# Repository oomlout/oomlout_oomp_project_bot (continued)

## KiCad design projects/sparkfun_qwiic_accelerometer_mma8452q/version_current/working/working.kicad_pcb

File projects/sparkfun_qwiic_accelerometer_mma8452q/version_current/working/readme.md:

# Qwiic_Accelerometer_MMA8452Q by sparkfun  
This is a harvested standardized copy of a project from github.  
The original project can be found at:  
https://github.com/sparkfun/Qwiic_Accelerometer_MMA8452Q  
Please consult that link for additional, details, files, and license information.  
Note: It was auto harvested and if the original repo had more than one board file or anything out of the ordinary the files here are likely not representative.

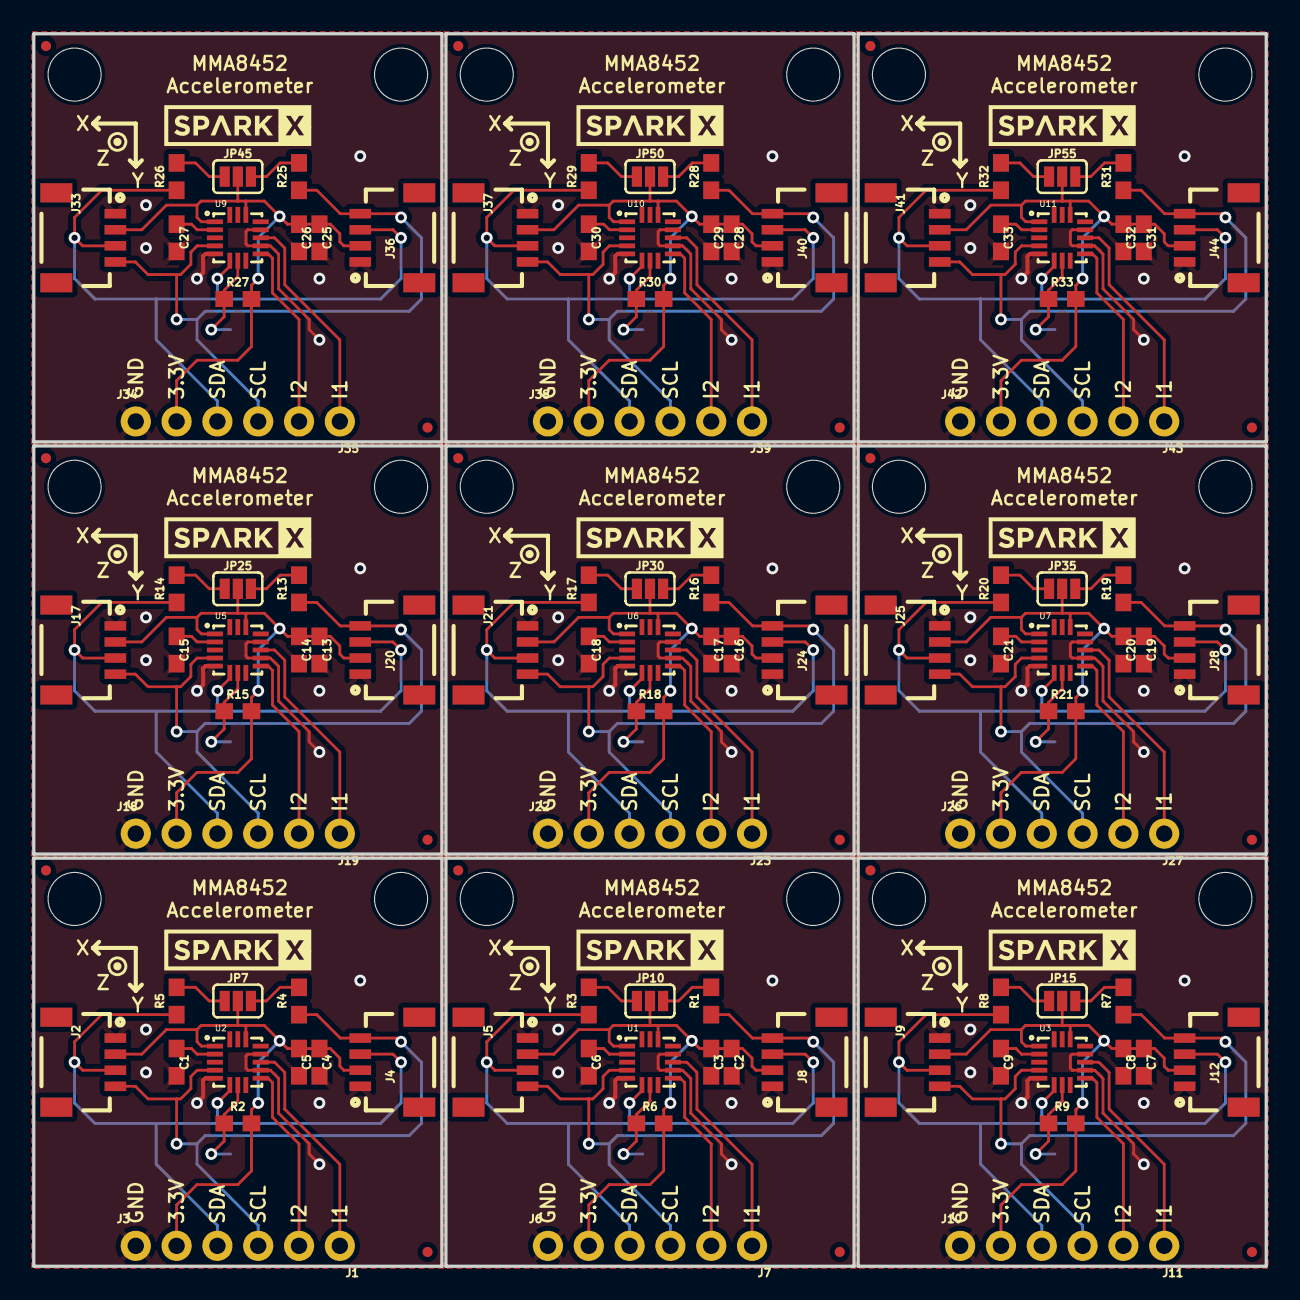
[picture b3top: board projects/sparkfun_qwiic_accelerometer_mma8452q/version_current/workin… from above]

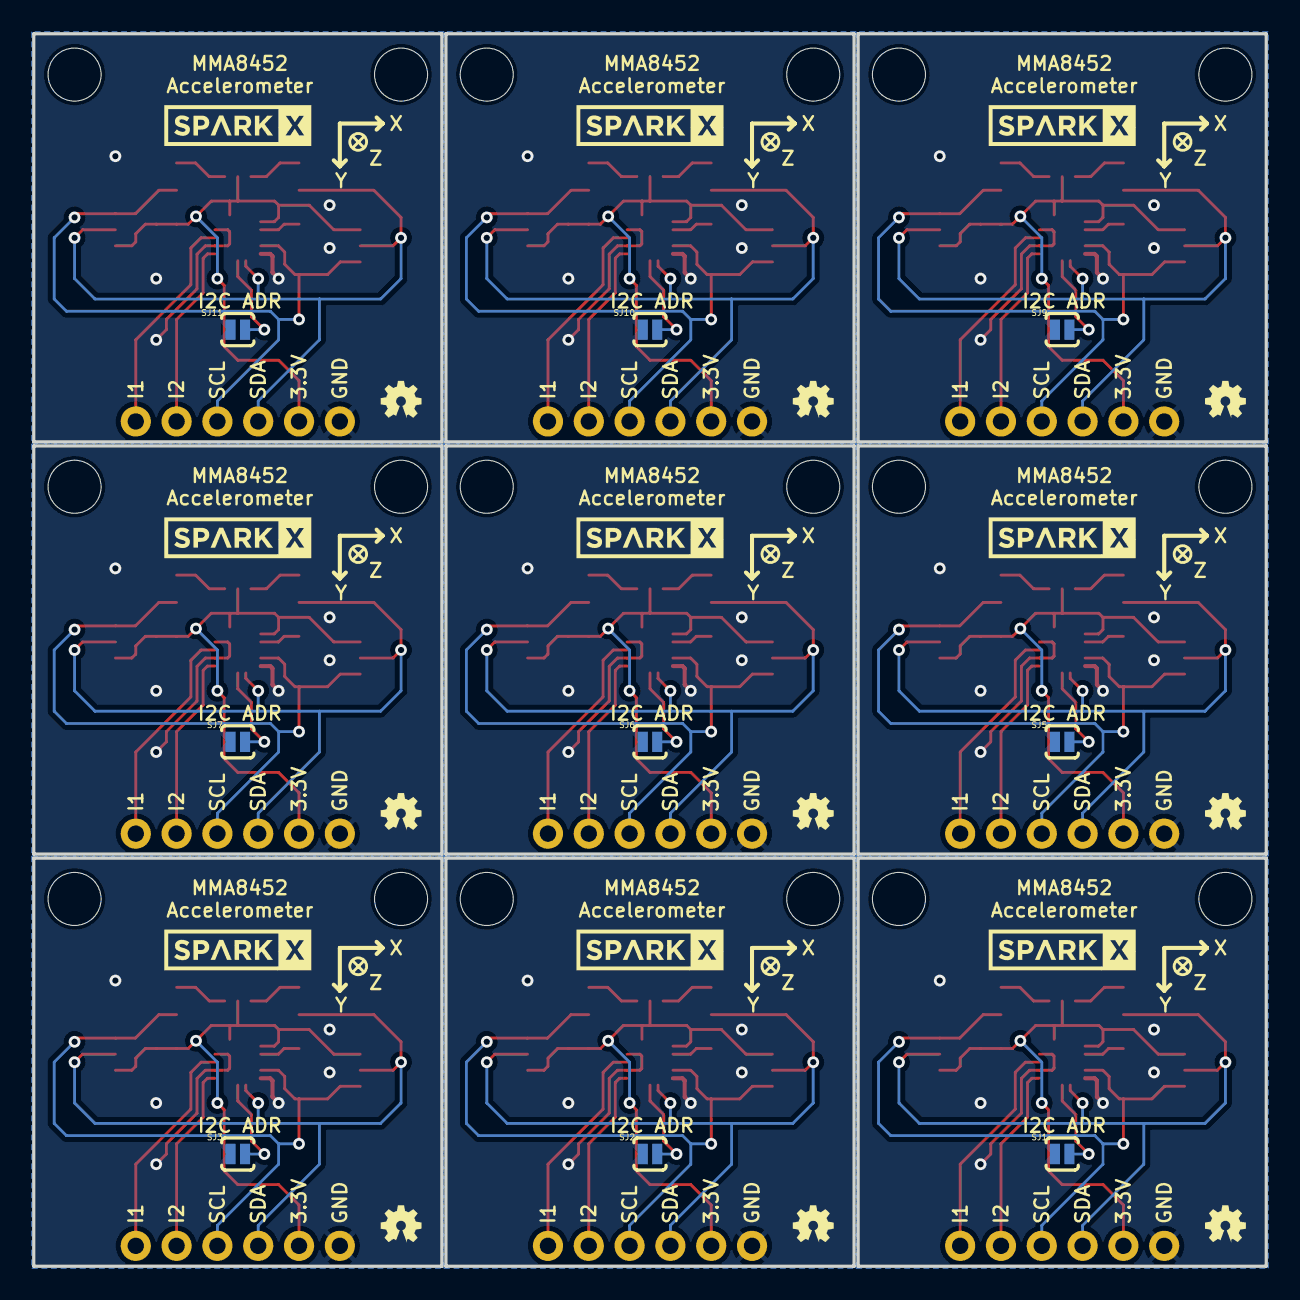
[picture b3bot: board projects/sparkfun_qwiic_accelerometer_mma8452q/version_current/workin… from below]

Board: 2 copper layers, 76.7 x 76.7 mm, 180 parts (27 on the bottom side), 90 nets.

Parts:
C1, C2, C4, C6, C7, C9, C13, C15, C16, C18, C19, C21, C25, C27, C28, C30, C31, C33: 0.1uF; 0603
C3, C5, C8, C14, C17, C20, C26, C29, C32: 4.7uF; 0603
J1, J7, J11, J19, J23, J27, J35, J39, J43: 1X02_NO_SILK
J2, J4, J5, J8, J9, J12, J17, J20, J21, J24, J25, J28, J33, J36, J37, J40, J41, J44: SMD; 1X04_1MM_RA
J3, J6, J10, J18, J22, J26, J34, J38, J42: PTH; 1X04_NO_SILK
JP1, JP3, JP4, JP5, JP11, JP12, JP21, JP22, JP26, JP27, JP31, JP32, JP41, JP42, JP46, JP47, JP51, JP52: STAND-OFF
JP2, JP6, JP8, JP9, JP13, JP14, JP23, JP24, JP28, JP29, JP33, JP34, JP43, JP44, JP48, JP49, JP53, JP54: FIDUCIALUFIDUCIAL; MICRO-FIDUCIAL
JP7, JP10, JP15, JP25, JP30, JP35, JP45, JP50, JP55: SMT-JUMPER_3_2-NC_PASTE_SILK
LOGO1, LOGO2, LOGO3, LOGO5, LOGO6, LOGO7, LOGO9, LOGO10, LOGO11: OSHW-LOGOMINI; OSHW-LOGO-MINI
R1, R3, R4, R5, R7, R8, R13, R14, R16, R17, R19, R20, R25, R26, R28, R29, R31, R32: 4.7k; 0603
R2, R6, R9, R15, R18, R21, R27, R30, R33: 10k; 0603
SJ1, SJ2, SJ3, SJ5, SJ6, SJ7, SJ9, SJ10, SJ11: SJ_2S-NO
U1, U2, U3, U5, U6, U7, U9, U10, U11: MMA8452Q; QFN-16_0.5MM
U$1, U$2, U$3, U$4, U$5, U$6, U$9, U$10, U$11, U$12, U$13, U$14, U$17, U$18, U$19, U$20, U$21, U$22: SPARKX-LOGO4; SPARKX-MEDIUM

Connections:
3.3V: C4.1, C5.1, J2.2, J3.2, J4.2, JP7.2, R2.2, U2.1, U2.14
3.3V1: C2.1, C3.1, J5.2, J6.2, J8.2, JP10.2, R6.2, U1.1, U1.14
3.3V2: C7.1, C8.1, J9.2, J10.2, J12.2, JP15.2, R9.2, U3.1, U3.14
3.3V4: C13.1, C14.1, J17.2, J18.2, J20.2, JP25.2, R15.2, U5.1, U5.14
3.3V5: C16.1, C17.1, J21.2, J22.2, J24.2, JP30.2, R18.2, U6.1, U6.14
3.3V6: C19.1, C20.1, J25.2, J26.2, J28.2, JP35.2, R21.2, U7.1, U7.14
3.3V8: C25.1, C26.1, J33.2, J34.2, J36.2, JP45.2, R27.2, U9.1, U9.14
3.3V9: C28.1, C29.1, J37.2, J38.2, J40.2, JP50.2, R30.2, U10.1, U10.14
3.3V10: C31.1, C32.1, J41.2, J42.2, J44.2, JP55.2, R33.2, U11.1, U11.14
BYP: C1.1, U2.2
BYP1: C6.1, U1.2
BYP2: C9.1, U3.2
BYP4: C15.1, U5.2
BYP5: C18.1, U6.2
BYP6: C21.1, U7.2
BYP8: C27.1, U9.2
BYP9: C30.1, U10.2
BYP10: C33.1, U11.2
GND: C1.2, C4.2, C5.2, J2.1, J3.1, J4.1, SJ1.1, U2.5, U2.10, U2.12
GND1: C2.2, C3.2, C6.2, J5.1, J6.1, J8.1, SJ2.1, U1.5, U1.10, U1.12
GND2: C7.2, C8.2, C9.2, J9.1, J10.1, J12.1, SJ3.1, U3.5, U3.10, U3.12
GND4: C13.2, C14.2, C15.2, J17.1, J18.1, J20.1, SJ5.1, U5.5, U5.10, U5.12
GND5: C16.2, C17.2, C18.2, J21.1, J22.1, J24.1, SJ6.1, U6.5, U6.10, U6.12
GND6: C19.2, C20.2, C21.2, J25.1, J26.1, J28.1, SJ7.1, U7.5, U7.10, U7.12
GND8: C25.2, C26.2, C27.2, J33.1, J34.1, J36.1, SJ9.1, U9.5, U9.10, U9.12
GND9: C28.2, C29.2, C30.2, J37.1, J38.1, J40.1, SJ10.1, U10.5, U10.10, U10.12
GND10: C31.2, C32.2, C33.2, J41.1, J42.1, J44.1, SJ11.1, U11.5, U11.10, U11.12
INT1: J1.1, U2.11
INT2: J1.2, U2.9
INT3: J7.2, U1.9
INT4: J7.1, U1.11
INT5: J11.2, U3.9
INT6: J11.1, U3.11
INT9: J19.2, U5.9
INT10: J19.1, U5.11
INT11: J23.2, U6.9
INT12: J23.1, U6.11
INT13: J27.2, U7.9
INT14: J27.1, U7.11
INT17: J35.2, U9.9
INT18: J35.1, U9.11
INT19: J39.2, U10.9
INT20: J39.1, U10.11
INT21: J43.2, U11.9
INT22: J43.1, U11.11
unnamed: JP7.1, R5.2
unnamed: JP7.3, R4.2
unnamed: JP10.1, R3.2
unnamed: JP10.3, R1.2
unnamed: JP15.1, R8.2
unnamed: JP15.3, R7.2
unnamed: JP25.1, R14.2
unnamed: JP25.3, R13.2
unnamed: JP30.1, R17.2
unnamed: JP30.3, R16.2
unnamed: JP35.1, R20.2
unnamed: JP35.3, R19.2
unnamed: JP45.1, R26.2
unnamed: JP45.3, R25.2
unnamed: JP50.1, R29.2
unnamed: JP50.3, R28.2
unnamed: JP55.1, R32.2
unnamed: JP55.3, R31.2
SA0: R2.1, SJ1.2, U2.7
SA1: R6.1, SJ2.2, U1.7
SA2: R9.1, SJ3.2, U3.7
SA4: R15.1, SJ5.2, U5.7
SA5: R18.1, SJ6.2, U6.7
SA6: R21.1, SJ7.2, U7.7
SA8: R27.1, SJ9.2, U9.7
SA9: R30.1, SJ10.2, U10.7
SA10: R33.1, SJ11.2, U11.7
SCL: J2.4, J3.4, J4.4, R4.1, U2.4
SCL1: J5.4, J6.4, J8.4, R1.1, U1.4
SCL2: J9.4, J10.4, J12.4, R7.1, U3.4
SCL4: J17.4, J18.4, J20.4, R13.1, U5.4
SCL5: J21.4, J22.4, J24.4, R16.1, U6.4
SCL6: J25.4, J26.4, J28.4, R19.1, U7.4
SCL8: J33.4, J34.4, J36.4, R25.1, U9.4
SCL9: J37.4, J38.4, J40.4, R28.1, U10.4
SCL10: J41.4, J42.4, J44.4, R31.1, U11.4
SDA: J2.3, J3.3, J4.3, R5.1, U2.6
SDA1: J5.3, J6.3, J8.3, R3.1, U1.6
SDA2: J9.3, J10.3, J12.3, R8.1, U3.6
SDA4: J17.3, J18.3, J20.3, R14.1, U5.6
SDA5: J21.3, J22.3, J24.3, R17.1, U6.6
SDA6: J25.3, J26.3, J28.3, R20.1, U7.6
SDA8: J33.3, J34.3, J36.3, R26.1, U9.6
SDA9: J37.3, J38.3, J40.3, R29.1, U10.6
SDA10: J41.3, J42.3, J44.3, R32.1, U11.6

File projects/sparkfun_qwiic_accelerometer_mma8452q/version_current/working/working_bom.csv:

"Id";"Designator";"Footprint";"Quantity";"Designation";"Supplier and ref";
1;"JP15,JP35,JP7,JP30,JP55,JP50,JP10,JP45,JP25";"SMT-JUMPER_3_2-NC_PASTE_SILK";9;"";;;
2;"R14,R28,R16,R1,R7,R5,R13,R4,R26,R25,R31,R17,R29,R8,R32,R3,R20,R19";"0603";18;"4.7k";;;
3;"C13,C2,C9,C16,C25,C19,C27,C30,C1,C7,C15,C4,C31,C33,C18,C28,C21,C6";"0603";18;"0.1uF";;;
4;"U10,U6,U7,U9,U1,U3,U2,U11,U5";"QFN-16_0.5MM";9;"MMA8452Q";;;
5;"J38,J10,J42,J3,J26,J6,J22,J34,J18";"1X04_NO_SILK";9;"PTH";;;
6;"C26,C14,C5,C20,C8,C3,C32,C29,C17";"0603";9;"4.7uF";;;
7;"J5,J33,J12,J44,J4,J36,J28,J37,J24,J2,J9,J25,J8,J17,J21,J20,J41,J40";"1X04_1MM_RA";18;"SMD";;;
8;"JP11,JP31,JP1,JP4,JP21,JP22,JP41,JP27,JP3,JP42,JP46,JP26,JP5,JP32,JP52,JP12,JP51,JP47";"STAND-OFF";18;"STAND-OFF";;;
9;"J11,J43,J39,J19,J23,J1,J7,J27,J35";"1X02_NO_SILK";9;"";;;
10;"JP14,JP48,JP8,JP6,JP53,JP33,JP13,JP34,JP44,JP29,JP9,JP28,JP43,JP49,JP54,JP2,JP24,JP23";"MICRO-FIDUCIAL";18;"FIDUCIALUFIDUCIAL";;;
11;"U$3,U$13,U$9,U$5,U$2,U$11,U$19,U$17,U$21,U$18,U$4,U$22,U$1,U$10,U$6,U$14,U$12,U$20";"SPARKX-MEDIUM";18;"SPARKX-LOGO4";;;
12;"R27,R33,R21,R15,R2,R6,R18,R30,R9";"0603";9;"10k";;;
13;"SJ5,SJ9,SJ10,SJ1,SJ11,SJ7,SJ2,SJ6,SJ3";"SJ_2S-NO";9;"";;;
14;"LOGO1,LOGO6,LOGO3,LOGO9,LOGO2,LOGO10,LOGO11,LOGO5,LOGO7";"OSHW-LOGO-MINI";9;"OSHW-LOGOMINI";;;

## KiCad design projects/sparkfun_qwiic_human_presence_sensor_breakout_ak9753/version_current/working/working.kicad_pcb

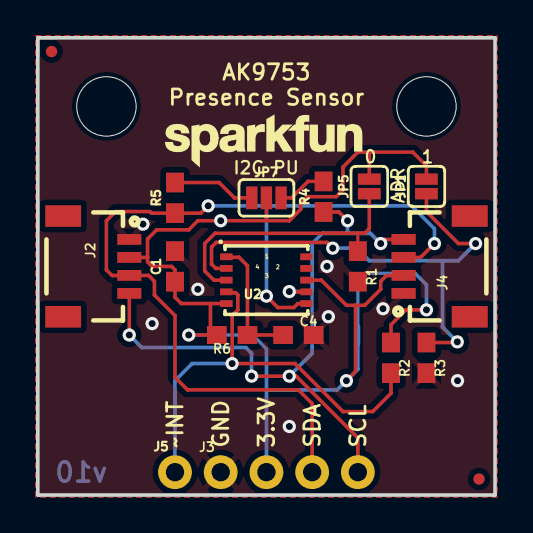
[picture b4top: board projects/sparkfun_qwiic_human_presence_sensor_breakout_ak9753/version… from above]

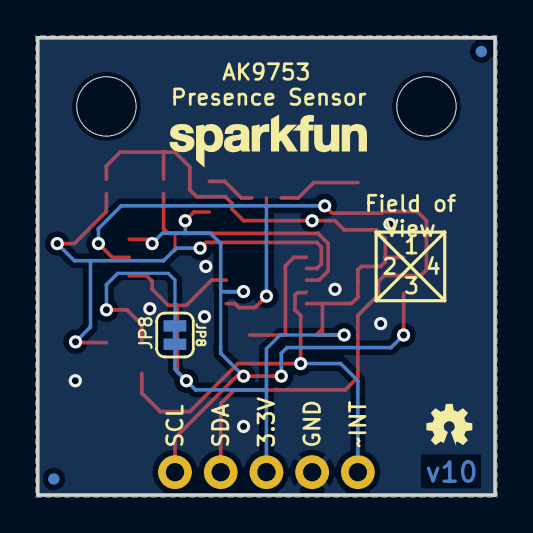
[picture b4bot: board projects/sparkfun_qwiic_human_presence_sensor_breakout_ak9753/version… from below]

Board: 2 copper layers, 25.4 x 25.4 mm, 28 parts (5 on the bottom side), 11 nets.

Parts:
C1, C4: 1.0uF; 0603
FRAME1: FRAME-LETTER; CREATIVE_COMMONS
J2, J4: 1X04_1MM_RA
J3: PTH; 1X04_NO_SILK
J5: 1X01_NO_SILK
JP1, JP5: SMT-JUMPER_2_NO_SILK
JP2, JP6, JP9, JP10: FIDUCIALUFIDUCIAL; MICRO-FIDUCIAL
JP3, JP4: STAND-OFF
JP7: SMT-JUMPER_3_2-NC_PASTE_SILK
JP8: SMT-JUMPER_2_NC_TRACE_SILK
LOGO1: OSHW-LOGOMINI; OSHW-LOGO-MINI
LOGO2: SFE_LOGO_NAME.1_INCH; SFE_LOGO_NAME_.1
LOGO3: REVISION
R1, R2, R3: 10k; 0603
R4, R5: 4.7k; 0603
R6: 330; 0603
U2: AK9753; SON10
U$2: SFE_LOGO_NAME_.1

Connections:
3.3V: C1.1, J2.2, J3.2, J4.2, JP1.2, JP5.2, JP7.2, JP8.2, R6.2, U2.3, U2.6
ADR0: JP1.1, R3.1, U2.9
ADR1: JP5.1, R1.1, U2.8
GND: C1.2, C4.2, J2.1, J3.1, J4.1, R1.2, R3.2, U2.1, U2.2
unnamed: JP7.1, R5.2
unnamed: JP7.3, R4.2
unnamed: JP8.1, R2.1
SCL: J2.4, J3.4, J4.4, R4.1, U2.4
SDA: J2.3, J3.3, J4.3, R5.1, U2.5
VDD: C4.1, R6.1, U2.10
~INT: J5.1, R2.2, U2.7

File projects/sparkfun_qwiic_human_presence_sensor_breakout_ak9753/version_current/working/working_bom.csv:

"Id";"Designator";"Footprint";"Quantity";"Designation";"Supplier and ref";
1;"C4,C1";"0603";2;"1.0uF";;;
2;"JP1,JP5";"SMT-JUMPER_2_NO_SILK";2;"";;;
3;"LOGO3";"REVISION";1;"REVISION";;;
4;"JP4,JP3";"STAND-OFF";2;"STAND-OFF";;;
5;"J4,J2";"1X04_1MM_RA";2;"";;;
6;"R2,R3,R1";"0603";3;"10k";;;
7;"R5,R4";"0603";2;"4.7k";;;
8;"U2";"SON10";1;"AK9753";;;
9;"FRAME1";"CREATIVE_COMMONS";1;"FRAME-LETTER";;;
10;"R6";"0603";1;"330";;;
11;"JP7";"SMT-JUMPER_3_2-NC_PASTE_SILK";1;"";;;
12;"JP2,JP6,JP9,JP10";"MICRO-FIDUCIAL";4;"FIDUCIALUFIDUCIAL";;;
13;"J3";"1X04_NO_SILK";1;"PTH";;;
14;"J5";"1X01_NO_SILK";1;"";;;
15;"LOGO2";"SFE_LOGO_NAME_.1";1;"SFE_LOGO_NAME.1_INCH";;;
16;"LOGO1";"OSHW-LOGO-MINI";1;"OSHW-LOGOMINI";;;
17;"JP8";"SMT-JUMPER_2_NC_TRACE_SILK";1;"";;;
18;"U$2";"SFE_LOGO_NAME_.1";1;"";;;

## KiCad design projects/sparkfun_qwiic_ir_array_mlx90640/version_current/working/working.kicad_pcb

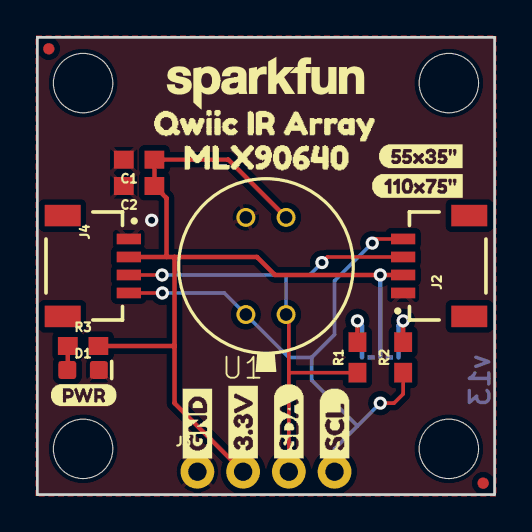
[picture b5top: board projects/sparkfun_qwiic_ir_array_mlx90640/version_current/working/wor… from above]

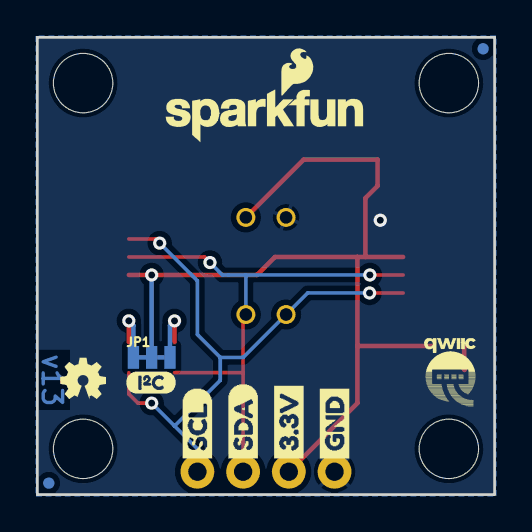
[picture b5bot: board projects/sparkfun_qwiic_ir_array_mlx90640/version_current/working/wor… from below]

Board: 2 copper layers, 25.4 x 25.4 mm, 39 parts (11 on the bottom side), 7 nets.

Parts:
C1: 0.1uF; 0603
C2: 1.0uF; 0603
D1: RED; LED-0603
FRAME1: FRAME-LETTER; CREATIVE_COMMONS
J2, J4: JST04_1MM_RA
J3: PTH; 1X04_NO_SILK
JP1: I2C; SMT-JUMPER_3_2-NC_TRACE_NO-SILK
JP2, JP5, JP6, JP7: FIDUCIALUFIDUCIAL; MICRO-FIDUCIAL
JP3, JP4, JP8, JP9: STAND-OFF
LOGO1: OSHW-LOGOMINI; OSHW-LOGO-MINI
LOGO2: SFE_LOGO_NAME_FLAME.1_INCH; SFE_LOGO_NAME_FLAME_.1
LOGO3: SFE_LOGO_NAME.1_INCH; SFE_LOGO_NAME_.1
LOGO4: REVISION
R1, R2: 2.2k; 0603
R3: 1k; 0603
U1: 110DEG; MLX90540_MLX90640
U$1, U$7: SDA-[)
U$3: 55X35#1
U$4, U$8: SCL-[)
U$5, U$9: 3.3V
U$6, U$10: GND-04
U$11: QWIIC-LOGO-SMALL
U$12: PWR-()-03
U$13: MLX906401
U$14: QWIIC_IR_ARRAY0
U$15: 110X75#0
U$16: I_SUPER2_C-()-03

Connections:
3.3V: C1.1, C2.1, J2.2, J3.2, J4.2, JP1.2, R3.2, U1.VDD
GND: C1.2, C2.2, D1.C, J2.1, J3.1, J4.1, U1.GND
unnamed: JP1.3, R1.2
unnamed: JP1.1, R2.2
unnamed: D1.A, R3.1
SCL: J2.4, J3.4, J4.4, R2.1, U1.SCL
SDA: J2.3, J3.3, J4.3, R1.1, U1.SDA

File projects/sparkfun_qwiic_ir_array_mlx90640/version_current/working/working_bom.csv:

"Id";"Designator";"Footprint";"Quantity";"Designation";"Supplier and ref";
1;"U$5,U$9";"3.3V";2;"";;;
2;"D1";"LED-0603";1;"RED";;;
3;"JP5,JP2,JP6,JP7";"MICRO-FIDUCIAL";4;"FIDUCIALUFIDUCIAL";;;
4;"C2";"0603";1;"1.0uF";;;
5;"C1";"0603";1;"0.1uF";;;
6;"U$12";"PWR-()-03";1;"";;;
7;"U$13";"MLX906401";1;"";;;
8;"JP4,JP3,JP8,JP9";"STAND-OFF";4;"STAND-OFF";;;
9;"R1,R2";"0603";2;"2.2k";;;
10;"LOGO4";"REVISION";1;"REVISION";;;
11;"FRAME1";"CREATIVE_COMMONS";1;"FRAME-LETTER";;;
12;"U$1,U$7";"SDA-[)";2;"";;;
13;"U$4,U$8";"SCL-[)";2;"";;;
14;"J2,J4";"JST04_1MM_RA";2;"";;;
15;"J3";"1X04_NO_SILK";1;"PTH";;;
16;"U$14";"QWIIC_IR_ARRAY0";1;"";;;
17;"R3";"0603";1;"1k";;;
18;"U$15";"110X75#0";1;"";;;
19;"U$3";"55X35#1";1;"";;;
20;"U1";"MLX90540_MLX90640";1;"110DEG";;;
21;"U$6,U$10";"GND-04";2;"";;;
22;"LOGO3";"SFE_LOGO_NAME_.1";1;"SFE_LOGO_NAME.1_INCH";;;
23;"LOGO2";"SFE_LOGO_NAME_FLAME_.1";1;"SFE_LOGO_NAME_FLAME.1_INCH";;;
24;"U$11";"QWIIC-LOGO-SMALL";1;"";;;
25;"U$16";"I_SUPER2_C-()-03";1;"";;;
26;"LOGO1";"OSHW-LOGO-MINI";1;"OSHW-LOGOMINI";;;
27;"JP1";"SMT-JUMPER_3_2-NC_TRACE_NO-SILK";1;"I2C";;;

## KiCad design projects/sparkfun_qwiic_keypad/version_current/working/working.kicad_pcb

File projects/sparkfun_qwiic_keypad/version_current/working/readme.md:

# Qwiic_Keypad by sparkfun  
This is a harvested standardized copy of a project from github.  
The original project can be found at:  
https://github.com/sparkfun/Qwiic_Keypad  
Please consult that link for additional, details, files, and license information.  
Note: It was auto harvested and if the original repo had more than one board file or anything out of the ordinary the files here are likely not representative.

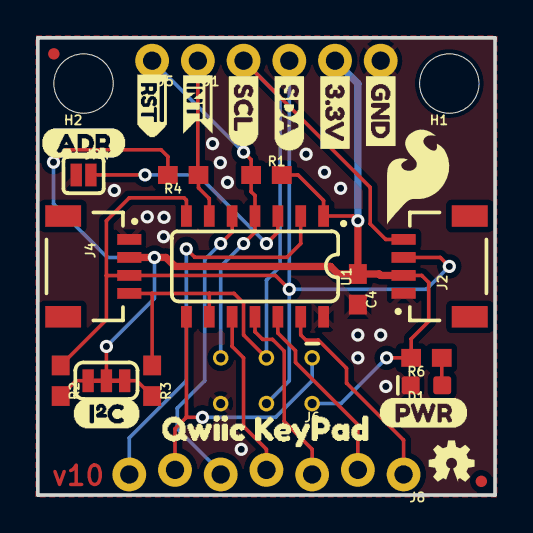
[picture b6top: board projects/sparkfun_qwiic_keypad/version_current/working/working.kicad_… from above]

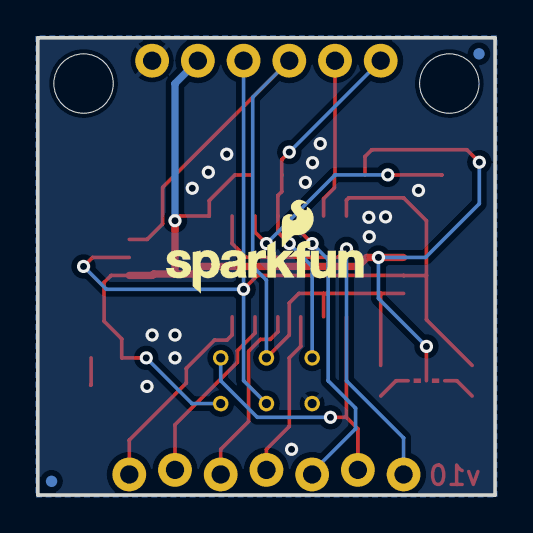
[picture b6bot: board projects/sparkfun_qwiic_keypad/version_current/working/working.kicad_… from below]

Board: 2 copper layers, 25.4 x 25.4 mm, 37 parts (3 on the bottom side), 17 nets.

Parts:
C4: 0.1uF; 0603
D1: RED; LED-0603
FRAME1: FRAME-LETTER; CREATIVE_COMMONS
H1, H2: STAND-OFF
I2C0: SMT-JUMPER_3_2-NC_TRACE_SILK
J1, J5: 1X01_NO_SILK
J2, J4: JST04_1MM_RA
J3: PTH; 1X04_NO_SILK
J6: AVR_SPI_PROG_3X2TESTPOINTS; 2X3_TEST_POINTS
J8: 1X07_LOCK_NO_SILK
JP1, JP2, JP3, JP6: FIDUCIALUFIDUCIAL; MICRO-FIDUCIAL
JP4: JUMPER-SMT_2_NO_SILK; SMT-JUMPER_2_NO_SILK
LOGO1: OSHW-LOGOMINI; OSHW-LOGO-MINI
LOGO2: SFE_LOGO_NAME_FLAME.1_INCH; SFE_LOGO_NAME_FLAME_.1
LOGO3: SFE_LOGO_FLAME.2_INCH; SFE_LOGO_FLAME_.2
R1, R4: 4.7k; 0603
R2, R3: 2.2k; 0603
R6: 1k; 0603
U1: ATTINY84; SO14
U$3: 3.3V
U$4: GND
U$5: SDA
U$6: SCL
U$8: (PWR)
U$9: (I_SUPER2_C)
U$10: (ADR)
U$11: #RST_
U$12: #INT1
U$15: QWIIC_KEYPAD0

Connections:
1: J8.1, U1.13
2: J8.2, U1.12
3: J8.3, U1.11
3.3V: C4.1, I2C0.2, J2.2, J3.2, J4.2, J6.2, R1.2, R4.2, R6.2, U1.1
4: J8.4, U1.10
5: J8.5, U1.5
7: J8.7, U1.2
ADD1: JP4.2, U1.3
GND: C4.2, D1.C, J2.1, J3.1, J4.1, J6.6, JP4.1, U1.14
MISO/6: J6.1, J8.6, U1.8
unnamed: D1.A, R6.1
unnamed: I2C0.3, R2.2
unnamed: I2C0.1, R3.2
SCL: J2.4, J3.4, J4.4, J6.3, R3.1, U1.9
SDA: J2.3, J3.3, J4.3, J6.4, R2.1, U1.7
~INT: J1.1, R4.1, U1.6
~RST: J5.1, J6.5, R1.1, U1.4
